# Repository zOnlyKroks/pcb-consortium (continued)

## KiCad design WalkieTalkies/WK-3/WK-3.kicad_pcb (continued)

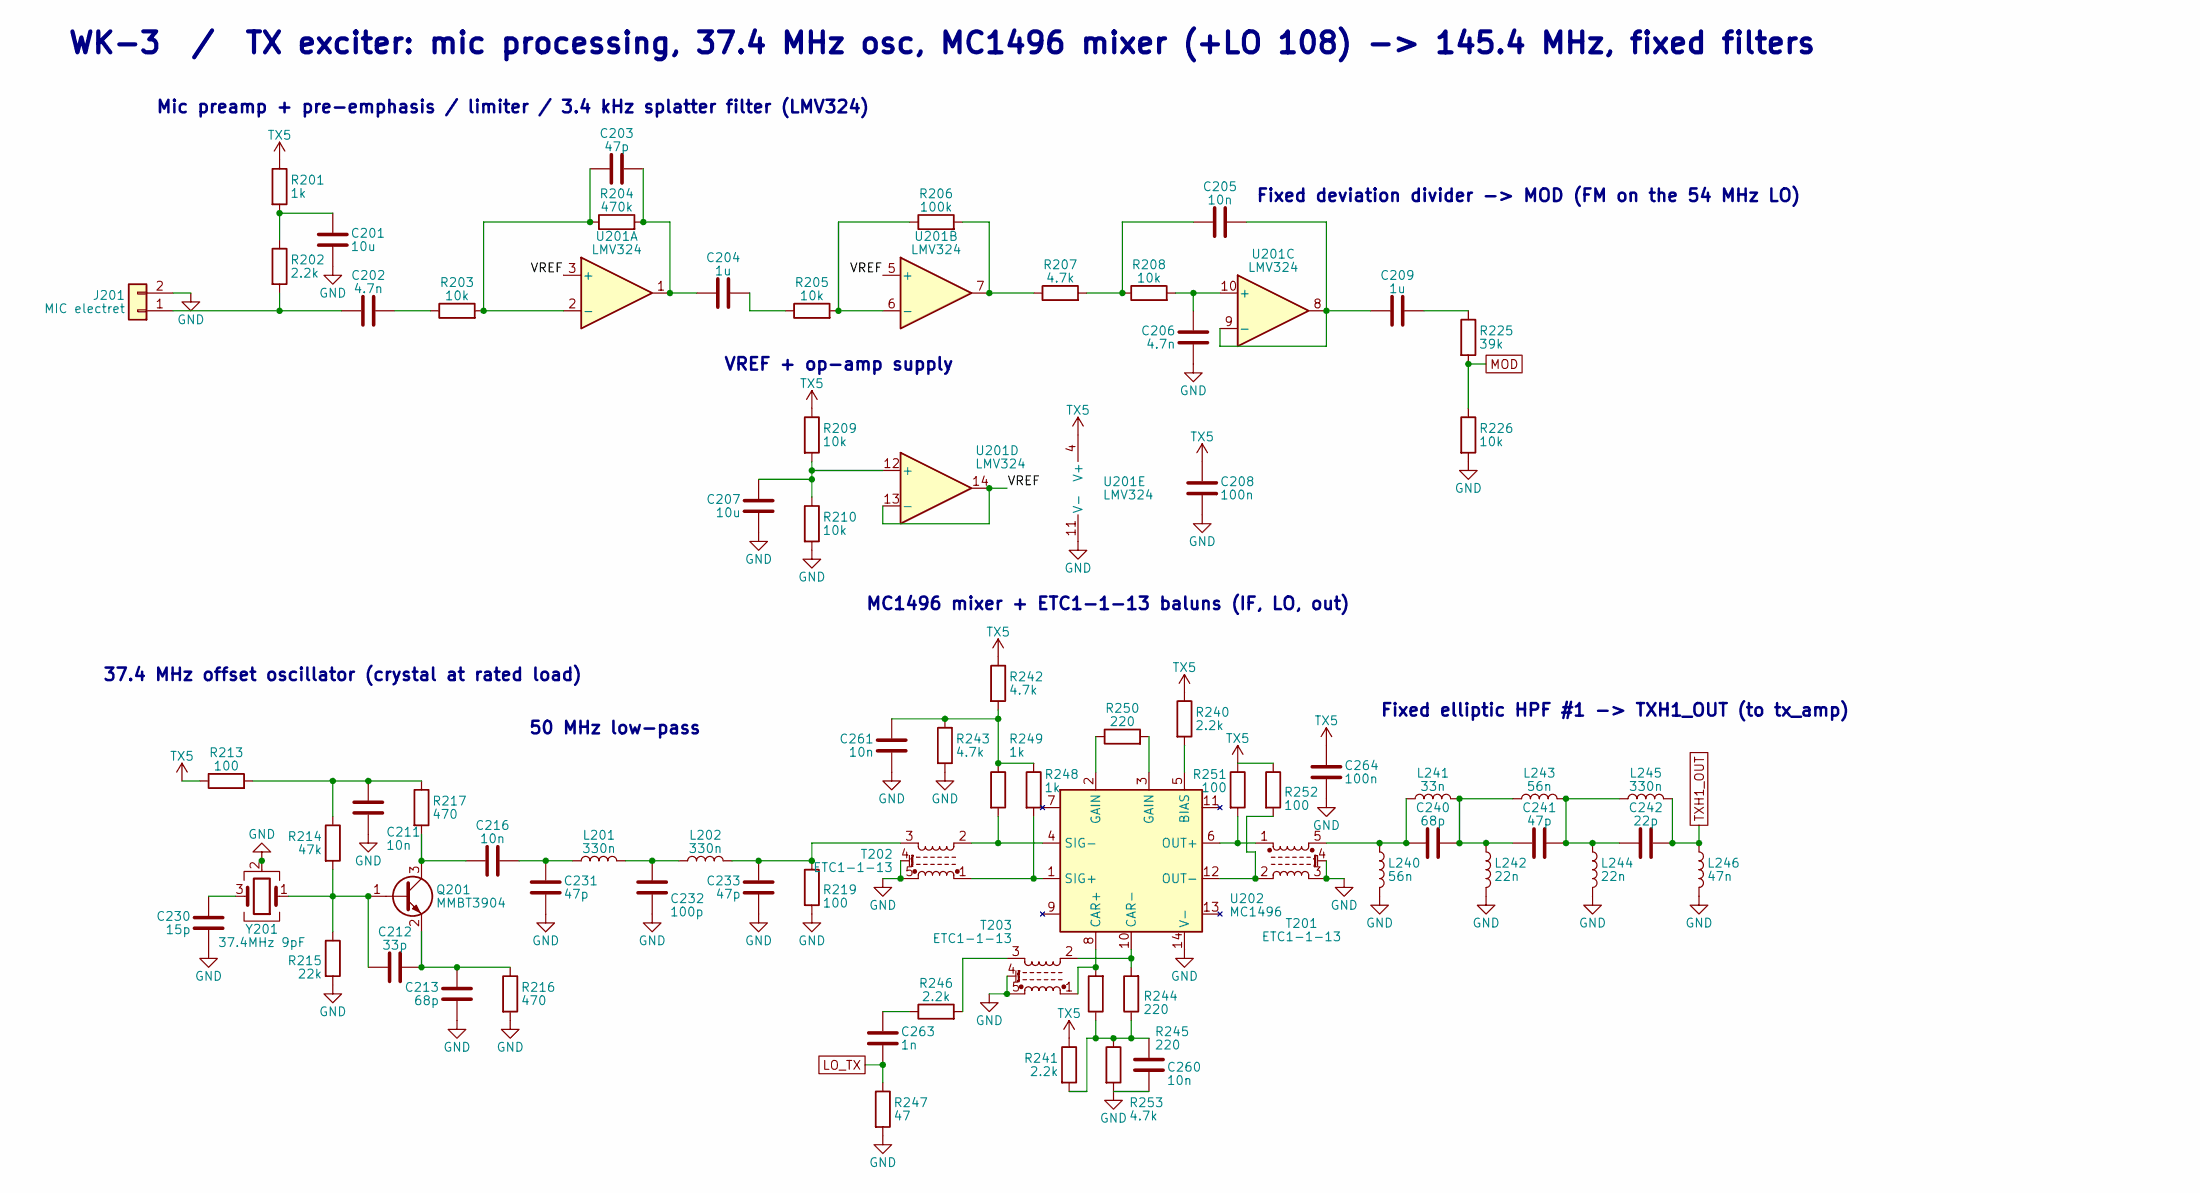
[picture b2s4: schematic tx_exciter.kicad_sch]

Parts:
C201, C207: 10u; C_0805_2012Metric; LCSC Part # C5448891
C202, C206: 4.7n; C_0603_1608Metric; LCSC Part # C53987
C203, C231, C233, C241: 47p; C_0603_1608Metric; LCSC Part # C1671
C204, C209: 1u; C_0603_1608Metric; LCSC Part # C15849
C205, C211, C216, C260, C261: 10n; C_0603_1608Metric; LCSC Part # C57112
C208, C264: 100n; C_0603_1608Metric; LCSC Part # C76711
C212: 33p; C_0603_1608Metric; LCSC Part # C1663
C213, C240: 68p; C_0603_1608Metric; LCSC Part # C62782
C230: 15p; C_0603_1608Metric; LCSC Part # C1644
C232: 100p; C_0603_1608Metric; LCSC Part # C14858
C242: 22p; C_0603_1608Metric; LCSC Part # C1653
C263: 1n; C_0603_1608Metric; LCSC Part # C1588
J201: MIC electret; JST_PH_B2B-PH-K_1x02_P2.00mm_Vertical; LCSC Part # C131337
L201, L202, L245: 330n; L_0805_2012Metric; LCSC Part # C6364716
L240, L243: 56n; L_0805_2012Metric; LCSC Part # C6808040
L241: 33n; L_0805_2012Metric; LCSC Part # C6808037
L242, L244: 22n; L_0805_2012Metric; LCSC Part # C6808033
L246: 47n; L_0805_2012Metric; LCSC Part # C6808039
Q201: MMBT3904; SOT-23; LCSC Part # C20526
R201, R248, R249: 1k; R_0603_1608Metric; LCSC Part # C21190
R202, R240, R241, R246: 2.2k; R_0603_1608Metric; LCSC Part # C4190
R203, R205, R208, R209, R210, R226: 10k; R_0603_1608Metric; LCSC Part # C2906982
R204: 470k; R_0603_1608Metric; LCSC Part # C23178
R206: 100k; R_0603_1608Metric; LCSC Part # C25803
R207, R242, R243, R253: 4.7k; R_0603_1608Metric; LCSC Part # C23162
R213, R219, R251, R252: 100; R_0603_1608Metric; LCSC Part # C22775
R214: 47k; R_0603_1608Metric; LCSC Part # C2907042
R215: 22k; R_0603_1608Metric; LCSC Part # C31850
R216, R217: 470; R_0603_1608Metric; LCSC Part # C23179
R225: 39k; R_0603_1608Metric; LCSC Part # C23153
R244, R245, R250: 220; R_0603_1608Metric; LCSC Part # C22962
R247: 47; R_0603_1608Metric; LCSC Part # C23182
T201, T202, T203: ETC1-1-13; Transformer_MACOM_SM-22; LCSC Part # C2834808
U201: LMV324; SOIC-14_3.9x8.7mm_P1.27mm; LCSC Part # C7974
U202: MC1496; SOIC-14_3.9x8.7mm_P1.27mm; LCSC Part # C512980
Y201: 37.4MHz 9pF; Crystal_SMD_3225-4Pin_3.2x2.5mm; LCSC Part # C368751

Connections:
/tx_exciter/VREF: U201.3 (+), U201.5 (+), U201.13 (-), U201.14
GND: C201.2, C206.2, C207.2, C208.2, C211.2, C213.2, C230.2, C231.2, C232.2, C233.2, C260.2, C261.2, C264.2, J201.2, L240.2, L242.2, L244.2, L246.2, R210.2, R215.2, R216.2, R219.2, R226.2, R243.2, R247.2, R253.2, T201.3, T201.4 (MP), T202.4 (MP), T202.5, T203.4 (MP), T203.5, U201.11 (V-), U202.14 (V-), Y201.2 (G), Y201.4 (G); also elsewhere on the board
LO_TX: C263.1, R247.1; also elsewhere on the board
MOD: R225.2, R226.1; also elsewhere on the board
unnamed: C201.1, R201.2, R202.1
unnamed: C202.2, R203.1
unnamed: C203.2, C204.1, R204.2, U201.1
unnamed: C204.2, R205.1
unnamed: C205.1, R207.2, R208.1
unnamed: C209.2, R225.1
unnamed: C211.1, R213.2, R214.1, R217.1
unnamed: C216.2, C231.1, L201.1
unnamed: C230.1, Y201.3
unnamed: C232.1, L201.2, L202.1
unnamed: C233.1, L202.2, R219.1, T202.3
unnamed: C240.1, L240.1, L241.1, T201.5
unnamed: C240.2, C241.1, L241.2, L242.1, L243.1
unnamed: C241.2, C242.1, L243.2, L244.1, L245.1
unnamed: C260.1, R241.2, R244.1, R245.1, R253.1
unnamed: C261.1, R242.2, R243.1, R248.1, R249.1
unnamed: C263.2, R246.1
unnamed: C202.1, J201.1, R202.2
unnamed: C212.1, Q201.1 (B), R214.2, R215.1, Y201.1
unnamed: C216.1, Q201.3 (C), R217.2
unnamed: C212.2, C213.1, Q201.2 (E), R216.1
unnamed: R206.2, R207.1, U201.7
unnamed: R246.2, T203.3
unnamed: R250.1, U202.2 (GAIN)
unnamed: R250.2, U202.3 (GAIN)
unnamed: C203.1, R203.2, R204.1, U201.2 (-)
unnamed: R205.2, R206.1, U201.6 (-)
unnamed: C206.1, R208.2, U201.10 (+)
unnamed: C205.2, C209.1, U201.8, U201.9 (-)
unnamed: C207.1, R209.2, R210.1, U201.12 (+)
unnamed: R240.2, U202.5 (BIAS)
unnamed: R244.2, T203.1, U202.8 (CAR+)
unnamed: R245.2, T203.2, U202.10 (CAR-)
unnamed: R251.2, T201.1, U202.6 (OUT+)
unnamed: R252.2, T201.2, U202.12 (OUT-)
unnamed: R248.2, T202.1, U202.1 (SIG+)
unnamed: R249.2, T202.2, U202.4 (SIG-)
TX5: C208.1, C264.1, R201.1, R209.1, R213.1, R240.1, R241.1, R242.1, R251.1, R252.1, U201.4 (V+); also elsewhere on the board
TXH1_OUT: C242.2, L245.2, L246.1; also elsewhere on the board

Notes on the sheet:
WK-3 / TX exciter: mic processing, 37.4 MHz osc, MC1496 mixer (+LO 108) -> 145.4 MHz, fixed filters
Mic preamp + pre-emphasis / limiter / 3.4 kHz splatter filter (LMV324)
Fixed deviation divider -> MOD (FM on the 54 MHz LO)
VREF + op-amp supply
37.4 MHz offset oscillator (crystal at rated load)
50 MHz low-pass
MC1496 mixer + ETC1-1-13 baluns (IF, LO, out)
Fixed elliptic HPF #1 -> TXH1_OUT (to tx_amp)

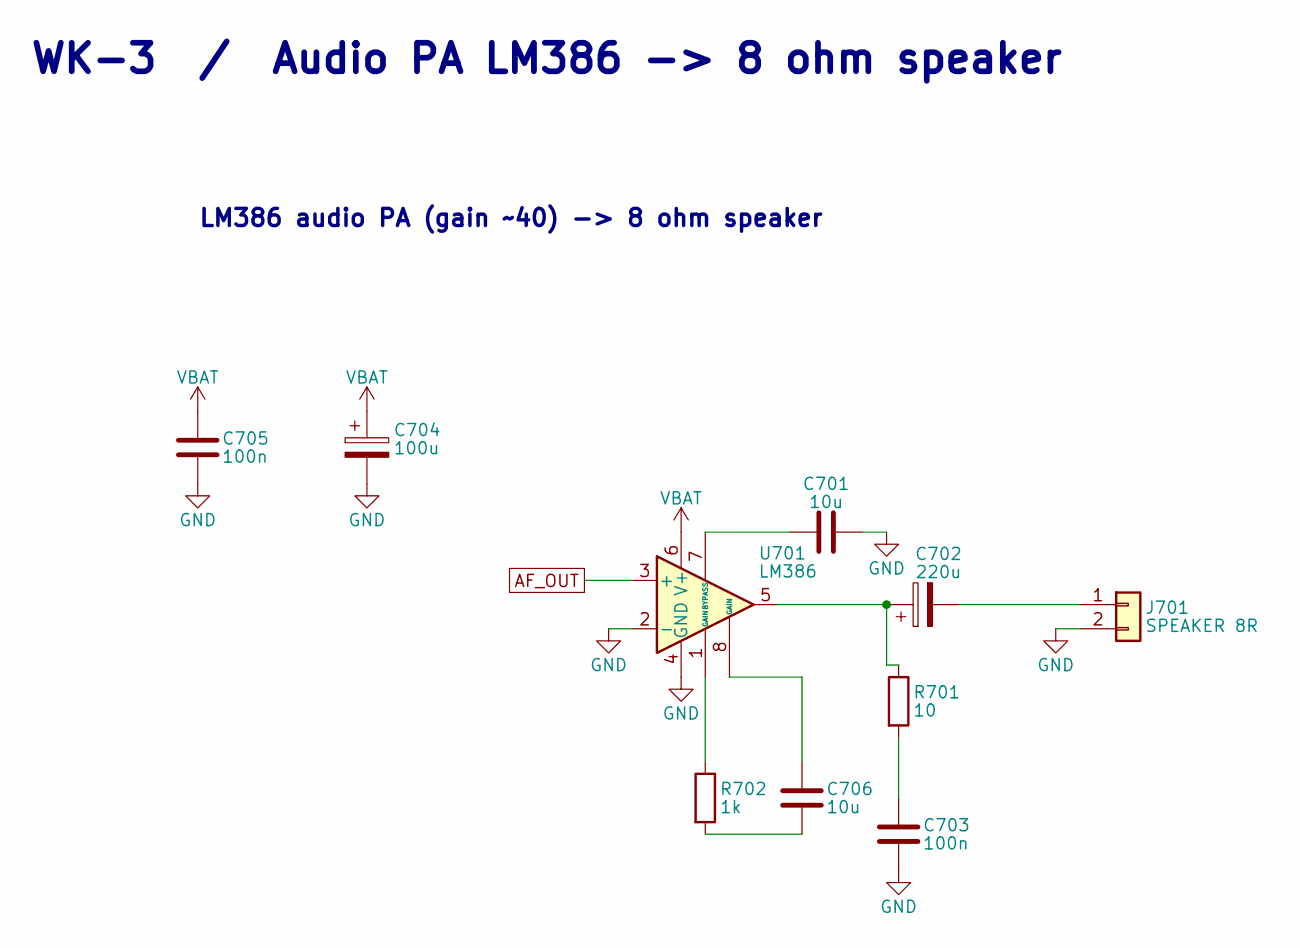
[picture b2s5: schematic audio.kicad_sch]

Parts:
C701, C706: 10u; C_0805_2012Metric; LCSC Part # C5448891
C702: 220u; CP_Elec_6.3x5.4; LCSC Part # C2887273
C703, C705: 100n; C_0603_1608Metric; LCSC Part # C76711
C704: 100u; CP_Elec_6.3x5.4; LCSC Part # C2887276
J701: SPEAKER 8R; JST_PH_B2B-PH-K_1x02_P2.00mm_Vertical; LCSC Part # C131337
R701: 10; R_0603_1608Metric; LCSC Part # C22859
R702: 1k; R_0603_1608Metric; LCSC Part # C21190
U701: LM386; SOIC-8_3.9x4.9mm_P1.27mm; LCSC Part # C23573

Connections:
AF_OUT: U701.3 (+); also elsewhere on the board
GND: C701.2, C703.2, C704.2, C705.2, J701.2, U701.2 (-), U701.4 (GND); also elsewhere on the board
unnamed: C702.1, R701.1, U701.5
unnamed: C703.1, R701.2
unnamed: C706.1, R702.2
unnamed: C706.2, U701.8 (GAIN)
unnamed: C702.2, J701.1
unnamed: R702.1, U701.1 (GAIN)
unnamed: C701.1, U701.7 (BYPASS)
VBAT: C704.1, C705.1, U701.6 (V+); also elsewhere on the board

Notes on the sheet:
LM386 audio PA (gain ~40) -> 8 ohm speaker
WK-3 / Audio PA LM386 -> 8 ohm speaker

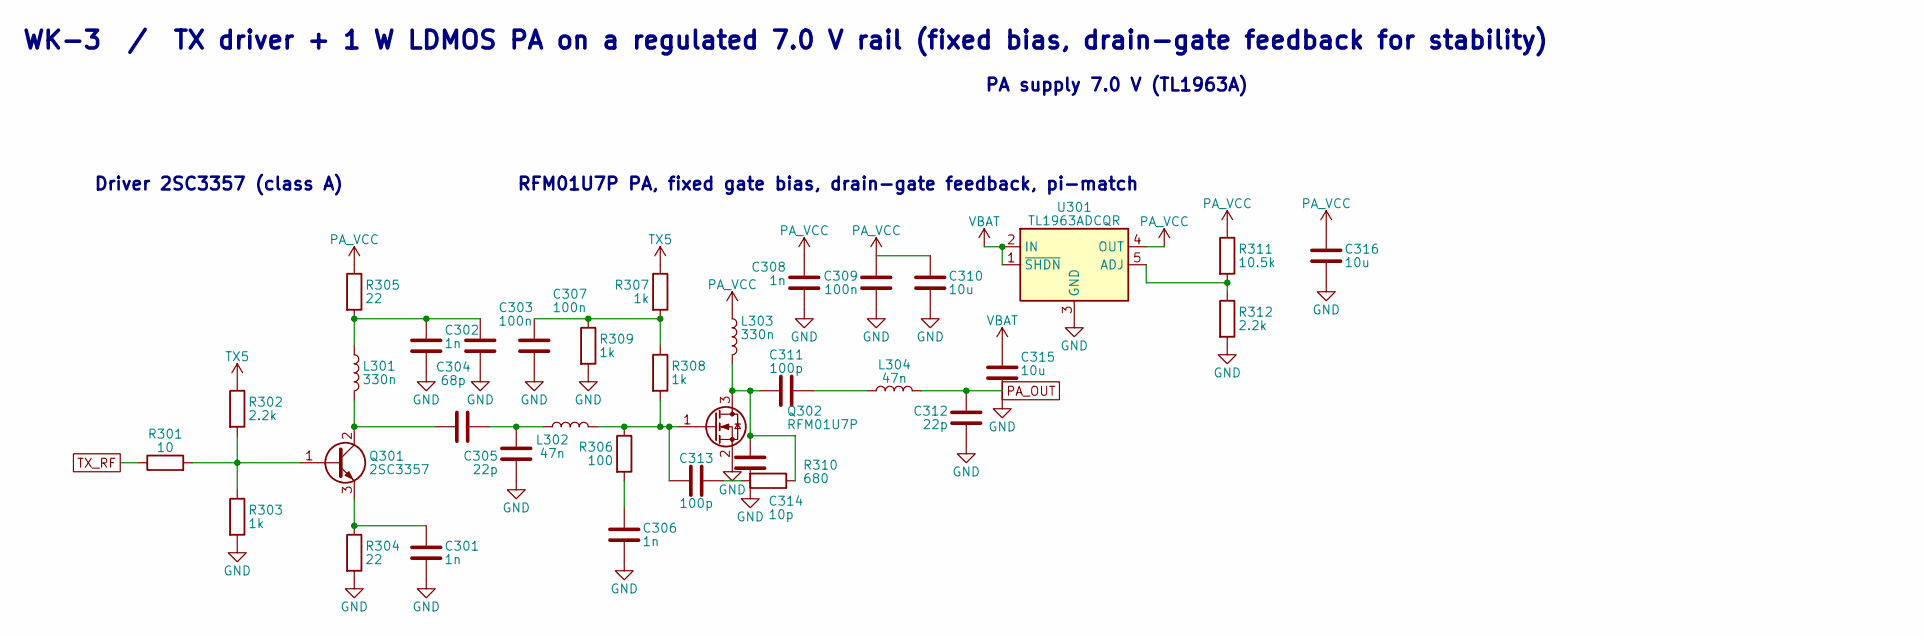
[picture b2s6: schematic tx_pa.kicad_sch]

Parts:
C301, C302, C306, C308: 1n; C_0603_1608Metric; LCSC Part # C1588
C303, C307, C309: 100n; C_0603_1608Metric; LCSC Part # C76711
C304: 68p; C_0603_1608Metric; LCSC Part # C62782
C305, C312: 22p; C_0603_1608Metric; LCSC Part # C1653
C310, C315, C316: 10u; C_0805_2012Metric; LCSC Part # C5448891
C311, C313: 100p; C_0603_1608Metric; LCSC Part # C14858
C314: 10p; C_0603_1608Metric; LCSC Part # C1634
L301: 330n; L_0805_2012Metric; LCSC Part # C6364716
L302, L304: 47n; L_0805_2012Metric; LCSC Part # C6808039
L303: 330n; L_1008_2520Metric; LCSC Part # C520207
Q301: 2SC3357; SOT-89-3; LCSC Part # C2987041
Q302: RFM01U7P; SOT-89-3; LCSC Part # C17561258
R301: 10; R_0603_1608Metric; LCSC Part # C22859
R302, R312: 2.2k; R_0603_1608Metric; LCSC Part # C4190
R303, R307, R308, R309: 1k; R_0603_1608Metric; LCSC Part # C21190
R304, R305: 22; R_0603_1608Metric; LCSC Part # C23345
R306: 100; R_0603_1608Metric; LCSC Part # C22775
R310: 680; R_0603_1608Metric; LCSC Part # C23228
R311: 10.5k; R_0603_1608Metric; LCSC Part # C22855
U301: TL1963ADCQR; SOT-223-6_TabPin3; LCSC Part # C86720

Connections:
GND: C301.2, C302.2, C303.2, C305.2, C306.2, C307.2, C308.2, C309.2, C310.2, C312.2, C314.2, C315.2, C316.2, Q302.2 (S), R303.2, R304.2, R309.2, R312.2, U301.3 (GND); also elsewhere on the board
unnamed: C302.1, C303.1, L301.1, R305.2
unnamed: C304.2, C305.1, L302.1
unnamed: C306.1, R306.2
unnamed: C307.1, R307.2, R308.1, R309.1
unnamed: C311.2, L304.1
unnamed: C313.1, R310.2
unnamed: Q301.1 (B), R301.2, R302.2, R303.1
unnamed: C304.1, L301.2, Q301.2 (C)
unnamed: C301.1, Q301.3 (E), R304.1
unnamed: C311.1, C314.1, L303.2, Q302.3 (D), R310.1
unnamed: C313.2, L302.2, Q302.1 (G), R306.1, R308.2
unnamed: R311.2, R312.1, U301.5 (ADJ)
PA_OUT: C312.1, L304.2; also elsewhere on the board
PA_VCC: C308.1, C309.1, C310.1, C316.1, L303.1, R305.1, R311.1, U301.4 (OUT)
TX5: R302.1, R307.1; also elsewhere on the board
TX_RF: R301.1; also elsewhere on the board
VBAT: C315.1, U301.1 (~SHDN), U301.2 (IN); also elsewhere on the board

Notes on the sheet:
WK-3 / TX driver + 1 W LDMOS PA on a regulated 7.0 V rail (fixed bias, drain-gate feedback for stability)
Driver 2SC3357 (class A)
RFM01U7P PA, fixed gate bias, drain-gate feedback, pi-match
PA supply 7.0 V (TL1963A)

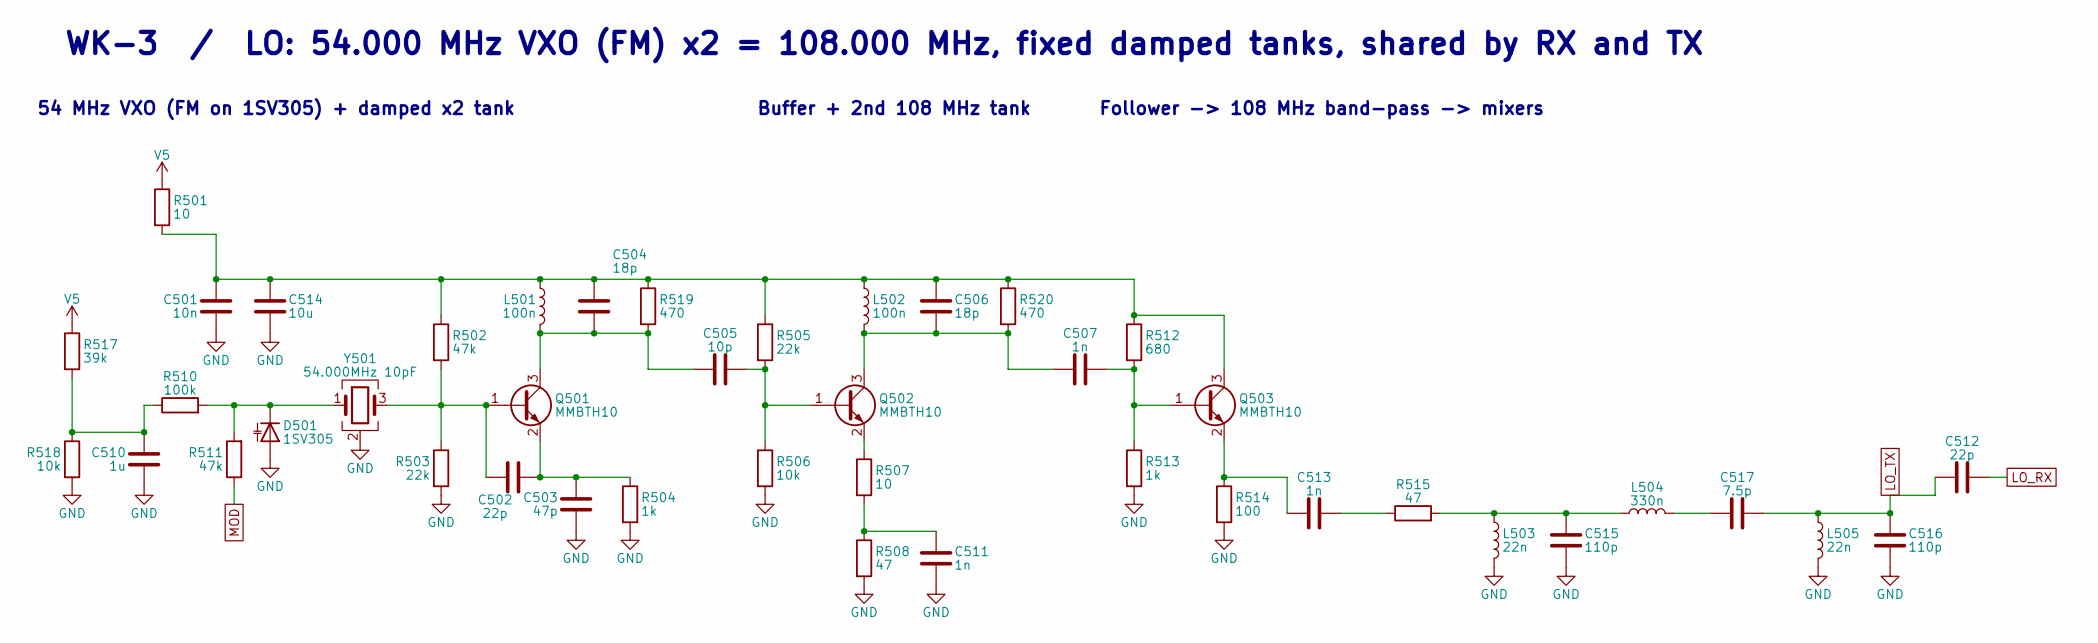
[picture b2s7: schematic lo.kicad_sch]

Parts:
C501: 10n; C_0603_1608Metric; LCSC Part # C57112
C502, C512: 22p; C_0603_1608Metric; LCSC Part # C1653
C503: 47p; C_0603_1608Metric; LCSC Part # C1671
C504, C506: 18p; C_0603_1608Metric; LCSC Part # C1647
C505: 10p; C_0603_1608Metric; LCSC Part # C1634
C507, C511, C513: 1n; C_0603_1608Metric; LCSC Part # C1588
C510: 1u; C_0603_1608Metric; LCSC Part # C15849
C514: 10u; C_0805_2012Metric; LCSC Part # C5448891
C515, C516: 110p; C_0603_1608Metric; LCSC Part # C327208
C517: 7.5p; C_0603_1608Metric; LCSC Part # C53424
D501: 1SV305; D_SOD-523; LCSC Part # C2762669
L501, L502: 100n; L_0805_2012Metric; LCSC Part # C6808047
L503, L505: 22n; L_0805_2012Metric; LCSC Part # C6808033
L504: 330n; L_0805_2012Metric; LCSC Part # C6364716
Q501, Q502, Q503: MMBTH10; SOT-23; LCSC Part # C22458951
R501, R507: 10; R_0603_1608Metric; LCSC Part # C22859
R502, R511: 47k; R_0603_1608Metric; LCSC Part # C2907042
R503, R505: 22k; R_0603_1608Metric; LCSC Part # C31850
R504, R513: 1k; R_0603_1608Metric; LCSC Part # C21190
R506, R518: 10k; R_0603_1608Metric; LCSC Part # C2906982
R508, R515: 47; R_0603_1608Metric; LCSC Part # C23182
R510: 100k; R_0603_1608Metric; LCSC Part # C25803
R512: 680; R_0603_1608Metric; LCSC Part # C23228
R514: 100; R_0603_1608Metric; LCSC Part # C22775
R517: 39k; R_0603_1608Metric; LCSC Part # C23153
R519, R520: 470; R_0603_1608Metric; LCSC Part # C23179
Y501: 54.000MHz 10pF; Crystal_SMD_3225-4Pin_3.2x2.5mm; LCSC Part # C252258

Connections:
GND: C501.2, C503.2, C510.2, C511.2, C514.2, C515.2, C516.2, D501.2 (A), L503.2, L505.2, R503.2, R504.2, R506.2, R508.2, R513.2, R514.2, R518.2, Y501.2 (G), Y501.4 (G); also elsewhere on the board
LO_RX: C512.2; also elsewhere on the board
LO_TX: C512.1, C516.1, C517.2, L505.1; also elsewhere on the board
MOD: R511.1; also elsewhere on the board
unnamed: C510.1, R510.1, R517.2, R518.1
unnamed: C511.1, R507.2, R508.1
unnamed: C513.2, R515.1
unnamed: C515.1, L503.1, L504.1, R515.2
unnamed: C517.1, L504.2
unnamed: D501.1 (K), R510.2, R511.2, Y501.1
unnamed: C502.1, Q501.1 (B), R502.2, R503.1, Y501.3
unnamed: C504.2, C505.1, L501.2, Q501.3 (C), R519.2
unnamed: C502.2, C503.1, Q501.2 (E), R504.1
unnamed: C505.2, Q502.1 (B), R505.2, R506.1
unnamed: C506.2, C507.1, L502.2, Q502.3 (C), R520.2
unnamed: Q502.2 (E), R507.1
unnamed: C507.2, Q503.1 (B), R512.2, R513.1
unnamed: C501.1, C504.1, C506.1, C514.1, L501.1, L502.1, Q503.3 (C), R501.2, R502.1, R505.1, R512.1, R519.1, R520.1
unnamed: C513.1, Q503.2 (E), R514.1
V5: R501.1, R517.1; also elsewhere on the board

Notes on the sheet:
54 MHz VXO (FM on 1SV305) + damped x2 tank
Buffer + 2nd 108 MHz tank
WK-3 / LO: 54.000 MHz VXO (FM) x2 = 108.000 MHz, fixed damped tanks, shared by RX and TX
Follower -> 108 MHz band-pass -> mixers

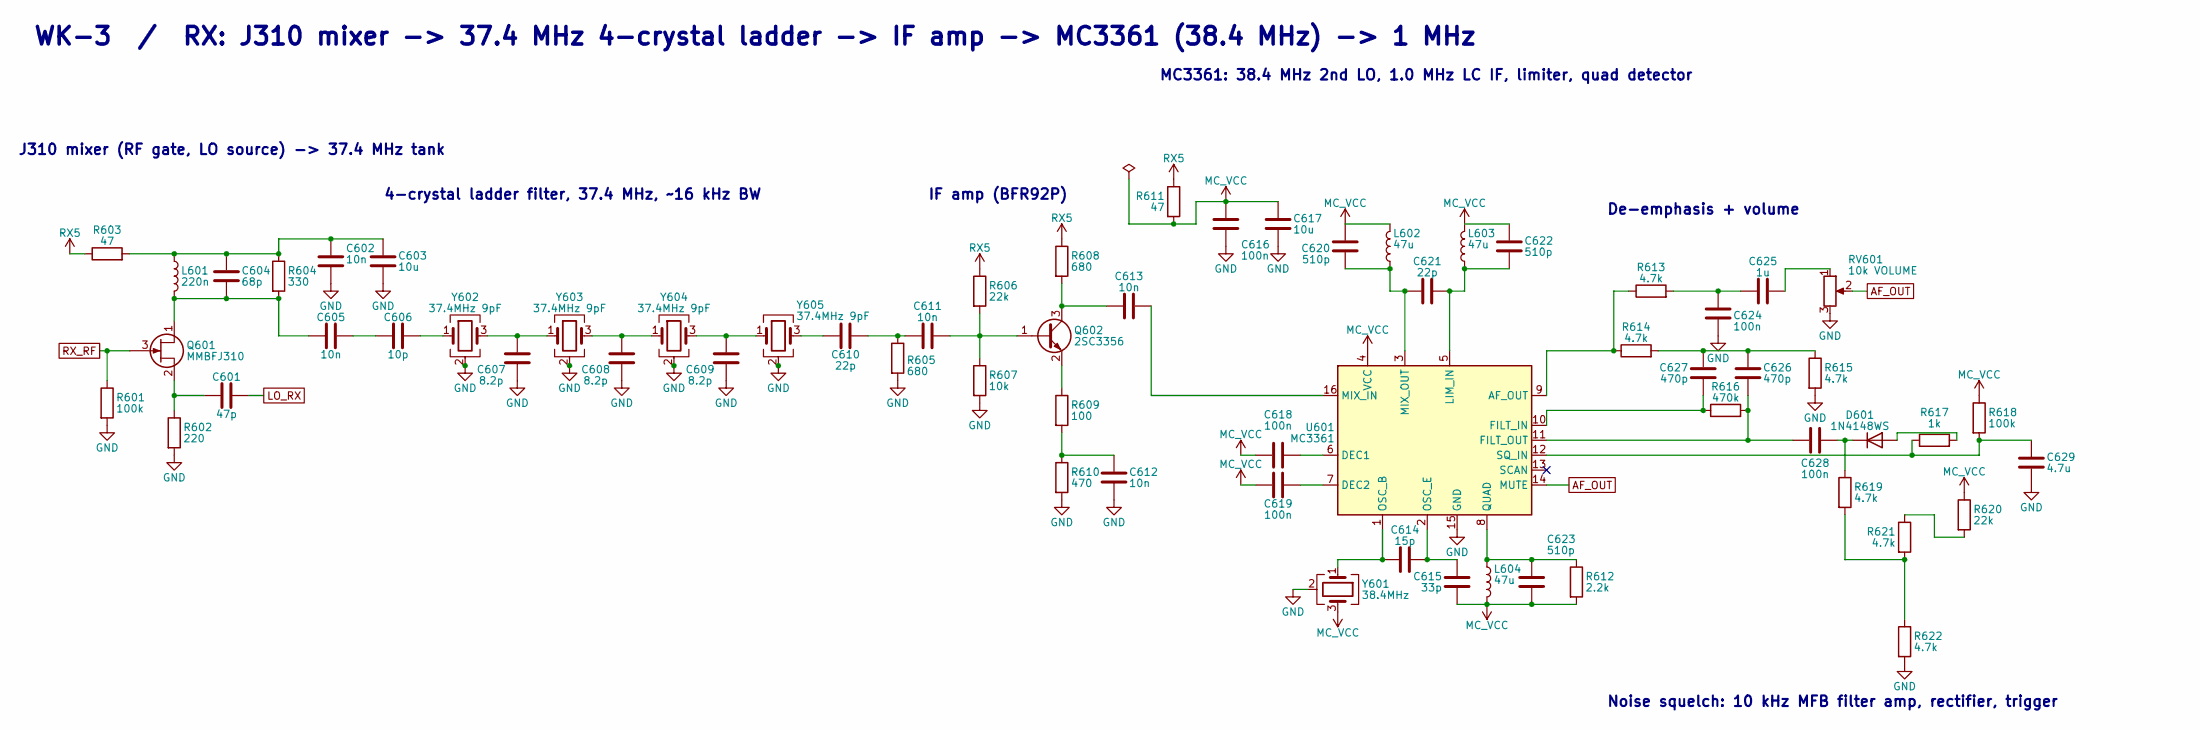
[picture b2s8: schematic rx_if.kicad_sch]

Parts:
C601: 47p; C_0603_1608Metric; LCSC Part # C1671
C602, C605, C611, C612, C613: 10n; C_0603_1608Metric; LCSC Part # C57112
C603, C617: 10u; C_0805_2012Metric; LCSC Part # C5448891
C604: 68p; C_0603_1608Metric; LCSC Part # C62782
C606: 10p; C_0603_1608Metric; LCSC Part # C1634
C607, C608, C609: 8.2p; C_0603_1608Metric; LCSC Part # C1685
C610, C621: 22p; C_0603_1608Metric; LCSC Part # C1653
C614: 15p; C_0603_1608Metric; LCSC Part # C1644
C615: 33p; C_0603_1608Metric; LCSC Part # C1663
C616, C618, C619, C624, C628: 100n; C_0603_1608Metric; LCSC Part # C76711
C620, C622, C623: 510p; C_0603_1608Metric; LCSC Part # C107052
C625: 1u; C_0603_1608Metric; LCSC Part # C15849
C626, C627: 470p; C_0603_1608Metric; LCSC Part # C106211
C629: 4.7u; C_0805_2012Metric; LCSC Part # C1779
D601: 1N4148WS; D_SOD-323; LCSC Part # C2128
L601: 220n; L_0805_2012Metric; LCSC Part # C2041935
L602, L603, L604: 47u; L_1210_3225Metric; LCSC Part # C66936
Q601: MMBFJ310; SOT-23; LCSC Part # C33416
Q602: 2SC3356; SOT-23; LCSC Part # C193010
R601, R618: 100k; R_0603_1608Metric; LCSC Part # C25803
R602: 220; R_0603_1608Metric; LCSC Part # C22962
R603, R611: 47; R_0603_1608Metric; LCSC Part # C23182
R604: 330; R_0603_1608Metric; LCSC Part # C23138
R605, R608: 680; R_0603_1608Metric; LCSC Part # C23228
R606, R620: 22k; R_0603_1608Metric; LCSC Part # C31850
R607: 10k; R_0603_1608Metric; LCSC Part # C2906982
R609: 100; R_0603_1608Metric; LCSC Part # C22775
R610: 470; R_0603_1608Metric; LCSC Part # C23179
R612: 2.2k; R_0603_1608Metric; LCSC Part # C4190
R613, R614, R615, R619, R621, R622: 4.7k; R_0603_1608Metric; LCSC Part # C23162
R616: 470k; R_0603_1608Metric; LCSC Part # C23178
R617: 1k; R_0603_1608Metric; LCSC Part # C21190
RV601: 10k VOLUME; Potentiometer_Alps_RK09K_Single_Vertical; LCSC Part # C351173
U601: MC3361; SOIC-16_3.9x9.9mm_P1.27mm; LCSC Part # C7302
Y601: 38.4MHz; Crystal_SMD_3225-4Pin_3.2x2.5mm; LCSC Part # C2901711
Y602, Y603, Y604, Y605: 37.4MHz 9pF; Crystal_SMD_3225-4Pin_3.2x2.5mm; LCSC Part # C368751

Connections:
AF_OUT: RV601.2, U601.14 (MUTE); also elsewhere on the board
GND: C602.2, C603.2, C607.2, C608.2, C609.2, C612.2, C616.2, C617.2, C624.2, C629.2, R601.2, R602.2, R605.2, R607.2, R610.2, R615.2, R622.2, RV601.3, U601.15 (GND), Y601.2 (G), Y601.4 (G), Y602.2 (G), Y602.4 (G), Y603.2 (G), Y603.4 (G), Y604.2 (G), Y604.4 (G), Y605.2 (G), Y605.4 (G); also elsewhere on the board
LO_RX: C601.1; also elsewhere on the board
MC_VCC: C615.2, C616.1, C617.1, C618.2, C619.2, C620.2, C622.2, C623.2, L602.2, L603.2, L604.2, R611.2, R612.2, R618.1, R620.1, U601.4 (VCC), Y601.3
unnamed: C602.1, C603.1, C604.1, L601.1, R603.2, R604.1
unnamed: C605.2, C606.1
unnamed: C606.2, Y602.1
unnamed: C607.1, Y602.3, Y603.1
unnamed: C608.1, Y603.3, Y604.1
unnamed: C609.1, Y604.3, Y605.1
unnamed: C610.1, Y605.3
unnamed: C610.2, C611.1, R605.1
unnamed: C612.1, R609.2, R610.1
unnamed: C624.1, C625.1, R613.2
unnamed: C625.2, RV601.1
unnamed: C626.1, C627.1, R614.2, R615.1
unnamed: D601.2 (A), R617.2
unnamed: C628.2, D601.1 (K), R619.1
unnamed: C604.2, C605.1, L601.2, Q601.1 (D), R604.2
unnamed: C601.2, Q601.2 (S), R602.1
unnamed: C611.2, Q602.1 (B), R606.2, R607.1
unnamed: C613.1, Q602.3 (C), R608.2
unnamed: Q602.2 (E), R609.1
unnamed: R619.2, R621.2, R622.1
unnamed: R620.2, R621.1
unnamed: R613.1, R614.1, U601.9 (AF_OUT)
unnamed: C618.1, U601.6 (DEC1)
unnamed: C619.1, U601.7 (DEC2)
unnamed: C627.2, R616.1, U601.10 (FILT_IN)
unnamed: C626.2, C628.1, R616.2, U601.11 (FILT_OUT)
unnamed: C621.2, C622.1, L603.1, U601.5 (LIM_IN)
unnamed: C613.2, U601.16 (MIX_IN)
unnamed: C620.1, C621.1, L602.1, U601.3 (MIX_OUT)
unnamed: C614.1, U601.1 (OSC_B), Y601.1
unnamed: C614.2, C615.1, U601.2 (OSC_E)
unnamed: C623.1, L604.1, R612.1, U601.8 (QUAD)
unnamed: C629.1, R617.1, R618.2, U601.12 (SQ_IN)
RX5: R603.1, R606.1, R608.1, R611.1; also elsewhere on the board
RX_RF: Q601.3 (G), R601.1; also elsewhere on the board

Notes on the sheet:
WK-3 / RX: J310 mixer -> 37.4 MHz 4-crystal ladder -> IF amp -> MC3361 (38.4 MHz) -> 1 MHz
J310 mixer (RF gate, LO source) -> 37.4 MHz tank
4-crystal ladder filter, 37.4 MHz, ~16 kHz BW
IF amp (BFR92P)
MC3361: 38.4 MHz 2nd LO, 1.0 MHz LC IF, limiter, quad detector
De-emphasis + volume
Noise squelch: 10 kHz MFB filter amp, rectifier, trigger

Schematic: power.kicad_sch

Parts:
BT101, BT102: BH-18650-B1BA002; BatteryHolder_MYOUNG_BH-18650-B1BA002; LCSC Part # C2988620
C101, C106, C107: 10u; C_0805_2012Metric; LCSC Part # C5448891
C102, C105, C108: 100n; C_0603_1608Metric; LCSC Part # C76711
C103: 10n; C_0603_1608Metric; LCSC Part # C57112
C104: 4.7u; C_0805_2012Metric; LCSC Part # C1779
D101: RED TX; LED_0603_1608Metric; LCSC Part # C2286
D102: RED PWR; LED_0603_1608Metric; LCSC Part # C2286
F101: 0.75A hold; Fuse_1206_3216Metric; LCSC Part # C976305
H101, H102, H103: M3; MountingHole_3.2mm_M3_Pad_Via
Q101, Q102, Q104, Q105: AO3401A; SOT-23; LCSC Part # C51953476
Q103: 2N7002; SOT-23; LCSC Part # C5224218
R101: 100k; R_0603_1608Metric; LCSC Part # C25803
R102, R103, R108: 10k; R_0603_1608Metric; LCSC Part # C2906982
R104: 1k; R_0603_1608Metric; LCSC Part # C21190
R105: 4.7k; R_0603_1608Metric; LCSC Part # C23162
R106: 2.2k; R_0603_1608Metric; LCSC Part # C4190
R107: 15.4k; R_0603_1608Metric; LCSC Part # C22804
R109: 180k; R_0603_1608Metric; LCSC Part # C22827
SW101: POWER; SW_SPDT_PCM12; LCSC Part # C221841
SW102: PTT; SW_SPST_TL3342; LCSC Part # C2886898
U101: LP2985-5.0; SOT-23-5; LCSC Part # C74511
U102: TL431AIDBZR; SOT-23; LCSC Part # C23892

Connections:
GND: BT101.2 (-), C101.2, C102.2, C103.2, C104.2, C105.2, C106.2, C107.2, C108.2, D101.1 (K), D102.1 (K), H101.1, H102.1, H103.1, Q103.2 (S), R101.2, R108.2, SW102.2, U101.2 (GND), U102.3 (A); also elsewhere on the board
unnamed: BT101.1 (+), BT102.2 (-)
unnamed: BT102.1 (+), F101.1
unnamed: D101.2 (A), R104.2
unnamed: D102.2 (A), R105.2
unnamed: F101.2, Q101.3 (D)
unnamed: Q101.1 (G), R101.1
unnamed: Q101.2 (S), Q105.2 (S), R106.1, SW101.1 (A)
unnamed: C105.1, Q102.1 (G), Q103.1 (G), R102.2, SW102.1
unnamed: Q103.3 (D), Q104.1 (G), R103.2
unnamed: Q105.1 (G), R106.2, U102.1 (K)
unnamed: R107.1, SW101.2 (B)
unnamed: C103.1, U101.4 (BP)
unnamed: C108.1, R107.2, R108.1, R109.2, U102.2 (REF)
RX5: C107.1, Q104.3 (D); also elsewhere on the board
TX5: C106.1, Q102.3 (D), R104.1; also elsewhere on the board
V5: C104.1, Q102.2 (S), Q104.2 (S), R102.1, R103.1, R105.1, U101.5 (VOUT); also elsewhere on the board
VBAT: C101.1, C102.1, Q105.3 (D), R109.1, U101.1 (VIN), U101.3 (ON/~OFF); also elsewhere on the board

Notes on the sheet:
WK-3 / Power + PTT switching
2 x 18650, reverse-polarity FET, power FET with under-voltage cut-off (TL431), 5 V LDO
PTT: pressed -> TX5 on, RX5 off

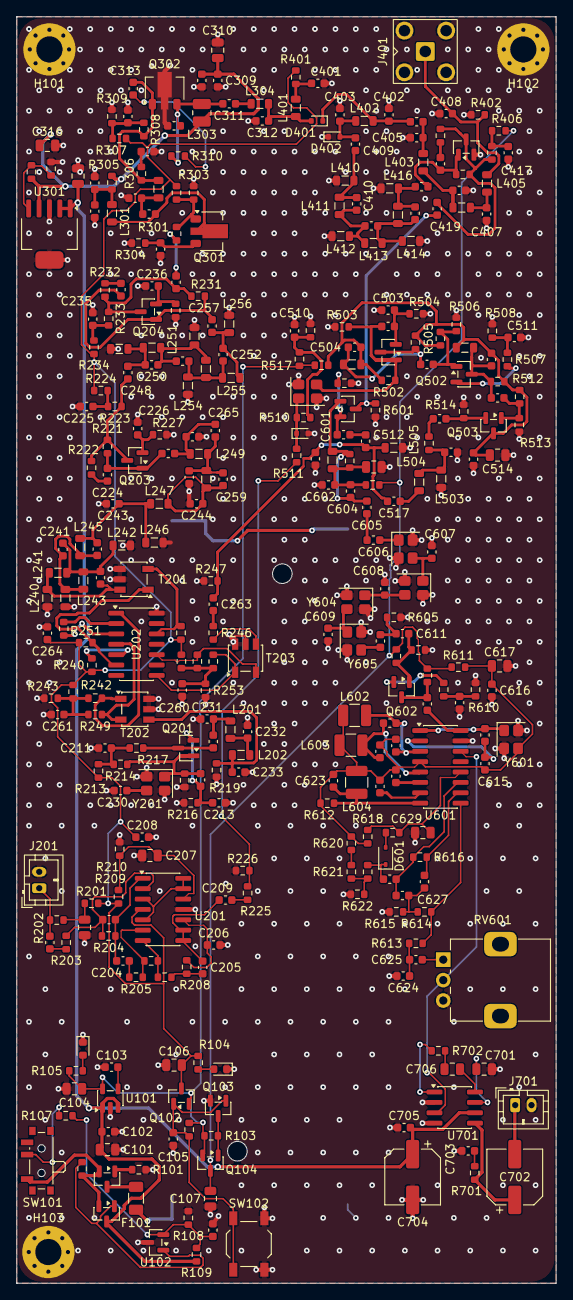
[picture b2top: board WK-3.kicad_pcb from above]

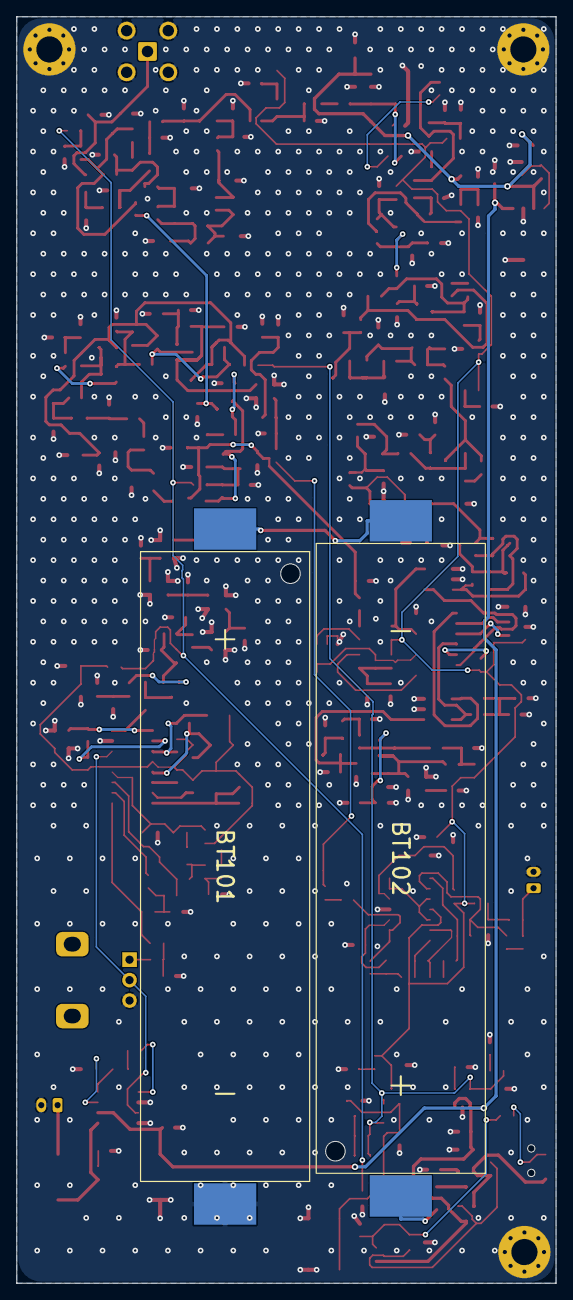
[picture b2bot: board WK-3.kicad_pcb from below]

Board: 4 copper layers, 66.0 x 155.0 mm, 339 parts (2 on the bottom side), 165 nets.

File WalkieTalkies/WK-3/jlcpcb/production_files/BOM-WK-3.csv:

Comment,Designator,Footprint,LCSC,Quantity
0.75A hold,F101,Fuse_1206_3216Metric,C976305,1
10,"R227,R237,R301,R501,R507,R701",R_0603_1608Metric,C22859,6
10.5k,R311,R_0603_1608Metric,C22855,1
100,"R213,R219,R233,R251,R252,R306,R514,R609",R_0603_1608Metric,C22775,8
100k,"R101,R206,R510,R601,R618",R_0603_1608Metric,C25803,5
100n,"L501,L502",L_0805_2012Metric,C6808047,2
100n,"C102,C105,C108,C208,C264,C303,C307,C309,C616,C618,C619,C624,C628,C703,C705",C_0603_1608Metric,C76711,15
100p,"C232,C311,C313",C_0603_1608Metric,C14858,3
100u,C704,CP_Elec_6.3x5.4,C2887276,1
10k,"R102,R103,R108,R203,R205,R208,R209,R210,R226,R231,R402,R506,R518,R607",R_0603_1608Metric,C2906982,14
10k VOLUME,RV601,Potentiometer_Alps_RK09K_Single_Vertical,C351173,1
10n,"C103,C205,C211,C216,C225,C235,C260,C261,C417,C501,C602,C605,C611,C612,C613",C_0603_1608Metric,C57112,15
10p,"C259,C314,C505,C606",C_0603_1608Metric,C1634,4
10u,"C101,C106,C107,C201,C207,C310,C315,C316,C514,C603,C617,C701,C706",C_0805_2012Metric,C5448891,13
110p,"C515,C516",C_0603_1608Metric,C327208,2
15.4k,R107,R_0603_1608Metric,C22804,1
15p,"C230,C614",C_0603_1608Metric,C1644,2
180k,R109,R_0603_1608Metric,C22827,1
18p,"C504,C506",C_0603_1608Metric,C1647,2
1N4148WS,D601,D_SOD-323,C2128,1
1SV305,D501,D_SOD-523,C2762669,1
1k,"R104,R201,R222,R232,R248,R249,R303,R307,R308,R309,R504,R513,R617,R702",R_0603_1608Metric,C21190,14
1n,"C224,C226,C234,C236,C247,C248,C257,C258,C263,C301,C302,C306,C308,C401,C404,C409,C414,C416,C419,C507,C511,C513",C_0603_1608Metric,C1588,22
1u,"C204,C209,C510,C625",C_0603_1608Metric,C15849,4
1u,L401,L_0805_2012Metric,C6808030,1
2.2k,"R106,R202,R240,R241,R246,R302,R312,R612",R_0603_1608Metric,C4190,8
22,"R234,R304,R305",R_0603_1608Metric,C23345,3
220,"R223,R244,R245,R250,R401,R602",R_0603_1608Metric,C22962,6
220n,L601,L_0805_2012Metric,C2041935,1
220u,C702,CP_Elec_6.3x5.4,C2887273,1
22k,"R215,R221,R503,R505,R606,R620",R_0603_1608Metric,C31850,6
22n,"L242,L244,L252,L254,L412,L414,L503,L505",L_0805_2012Metric,C6808033,8
22p,"C242,C252,C305,C312,C402,C403,C412,C502,C512,C610,C621",C_0603_1608Metric,C1653,11
2N7002,Q103,SOT-23,C5224218,1
2SC3356,"Q203,Q204,Q401,Q602",SOT-23,C193010,4
2SC3357,Q301,SOT-89-3,C2987041,1
330,R604,R_0603_1608Metric,C23138,1
330n,L303,L_1008_2520Metric,C520207,1
330n,"L201,L202,L245,L255,L301,L415,L504",L_0805_2012Metric,C6364716,7
33n,"L241,L251,L411",L_0805_2012Metric,C6808037,3
33p,"C212,C243,C244,C245,C246,C405,C408,C615",C_0603_1608Metric,C1663,8
37.4MHz 9pF,"Y201,Y602,Y603,Y604,Y605",Crystal_SMD_3225-4Pin_3.2x2.5mm,C368751,5
38.4MHz,Y601,Crystal_SMD_3225-4Pin_3.2x2.5mm,C2901711,1
39k,"R225,R517",R_0603_1608Metric,C23153,2
4.7k,"R105,R207,R242,R243,R253,R613,R614,R615,R619,R621,R622",R_0603_1608Metric,C23162,11
4.7n,"C202,C206",C_0603_1608Metric,C53987,2
4.7u,"C104,C629",C_0805_2012Metric,C1779,2
47,"R224,R247,R406,R508,R515,R603,R611",R_0603_1608Metric,C23182,7
470,"R216,R217,R405,R519,R520,R610",R_0603_1608Metric,C23179,6
470k,"R204,R616",R_0603_1608Metric,C23178,2
470p,"C626,C627",C_0603_1608Metric,C106211,2
47k,"R214,R403,R502,R511",R_0603_1608Metric,C2907042,4
47n,"L246,L249,L256,L302,L304,L416",L_0805_2012Metric,C6808039,6
47p,"C203,C231,C233,C241,C251,C406,C407,C411,C503,C601",C_0603_1608Metric,C1671,10
47u,"L602,L603,L604",L_1210_3225Metric,C66936,3
510p,"C620,C622,C623",C_0603_1608Metric,C107052,3
54.000MHz 10pF,Y501,Crystal_SMD_3225-4Pin_3.2x2.5mm,C252258,1
56n,"L240,L243,L248,L250,L253,L402,L403,L405,L410,L413",L_0805_2012Metric,C6808040,10
680,"R310,R404,R512,R605,R608",R_0603_1608Metric,C23228,5
68n,"L247,L404",L_0805_2012Metric,C6808042,2
68p,"C213,C240,C250,C304,C410,C604",C_0603_1608Metric,C62782,6
7.5p,C517,C_0603_1608Metric,C53424,1
8.2p,"C265,C607,C608,C609",C_0603_1608Metric,C1685,4
AO3401A,"Q101,Q102,Q104,Q105",SOT-23,C51953476,4
BAR64-02V,"D401,D402",D_SOD-523,C5295579,2
BH-18650-B1BA002,"BT101,BT102",BatteryHolder_MYOUNG_BH-18650-B1BA002,C2988620,2
ETC1-1-13,"T201,T202,T203",Transformer_MACOM_SM-22,C2834808,3
LM386,U701,SOIC-8_3.9x4.9mm_P1.27mm,C23573,1
LMV324,U201,SOIC-14_3.9x8.7mm_P1.27mm,C7974,1
LP2985-5.0,U101,SOT-23-5,C74511,1
MC1496,U202,SOIC-14_3.9x8.7mm_P1.27mm,C512980,1
MC3361,U601,SOIC-16_3.9x9.9mm_P1.27mm,C7302,1
MIC electret,J201,JST_PH_B2B-PH-K_1x02_P2.00mm_Vertical,C131337,1
MMBFJ310,Q601,SOT-23,C33416,1
MMBT3904,Q201,SOT-23,C20526,1
MMBTH10,"Q501,Q502,Q503",SOT-23,C22458951,3
POWER,SW101,SW_SPDT_PCM12,C221841,1
PTT,SW102,SW_SPST_TL3342,C2886898,1
RED PWR,D102,LED_0603_1608Metric,C2286,1
RED TX,D101,LED_0603_1608Metric,C2286,1
RFM01U7P,Q302,SOT-89-3,C17561258,1
SMA ANT,J401,SMA_BAT_Wireless_BWSMA-KWE-Z001,C496551,1
SPEAKER 8R,J701,JST_PH_B2B-PH-K_1x02_P2.00mm_Vertical,C131337,1
TL1963ADCQR,U301,SOT-223-6_TabPin3,C86720,1
TL431AIDBZR,U102,SOT-23,C23892,1
